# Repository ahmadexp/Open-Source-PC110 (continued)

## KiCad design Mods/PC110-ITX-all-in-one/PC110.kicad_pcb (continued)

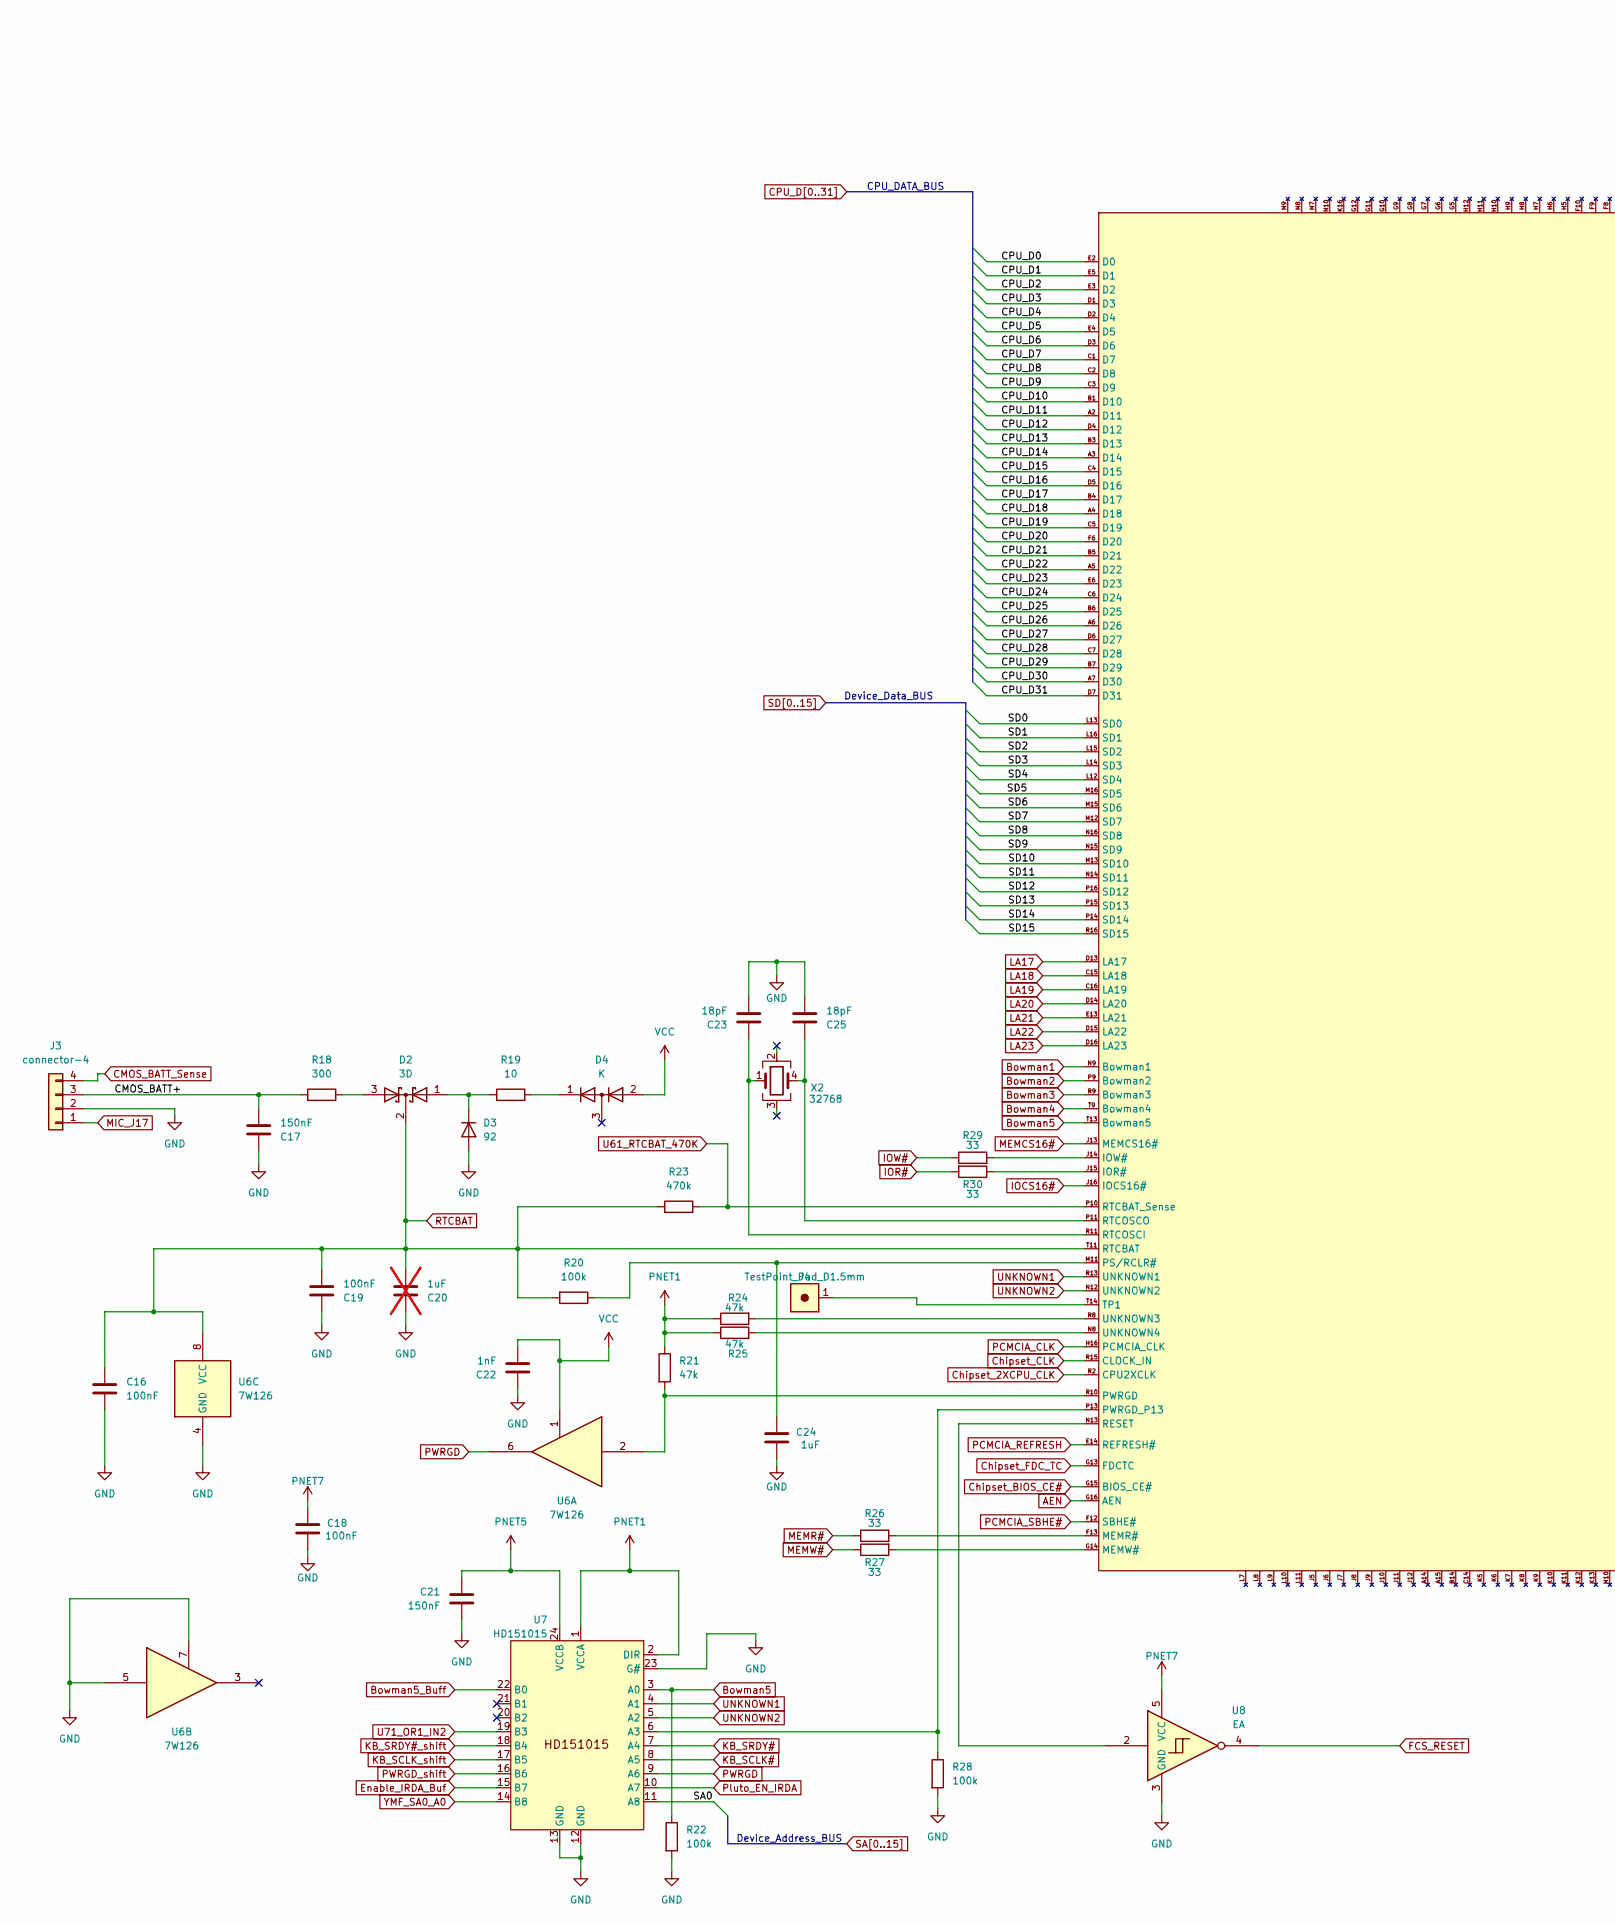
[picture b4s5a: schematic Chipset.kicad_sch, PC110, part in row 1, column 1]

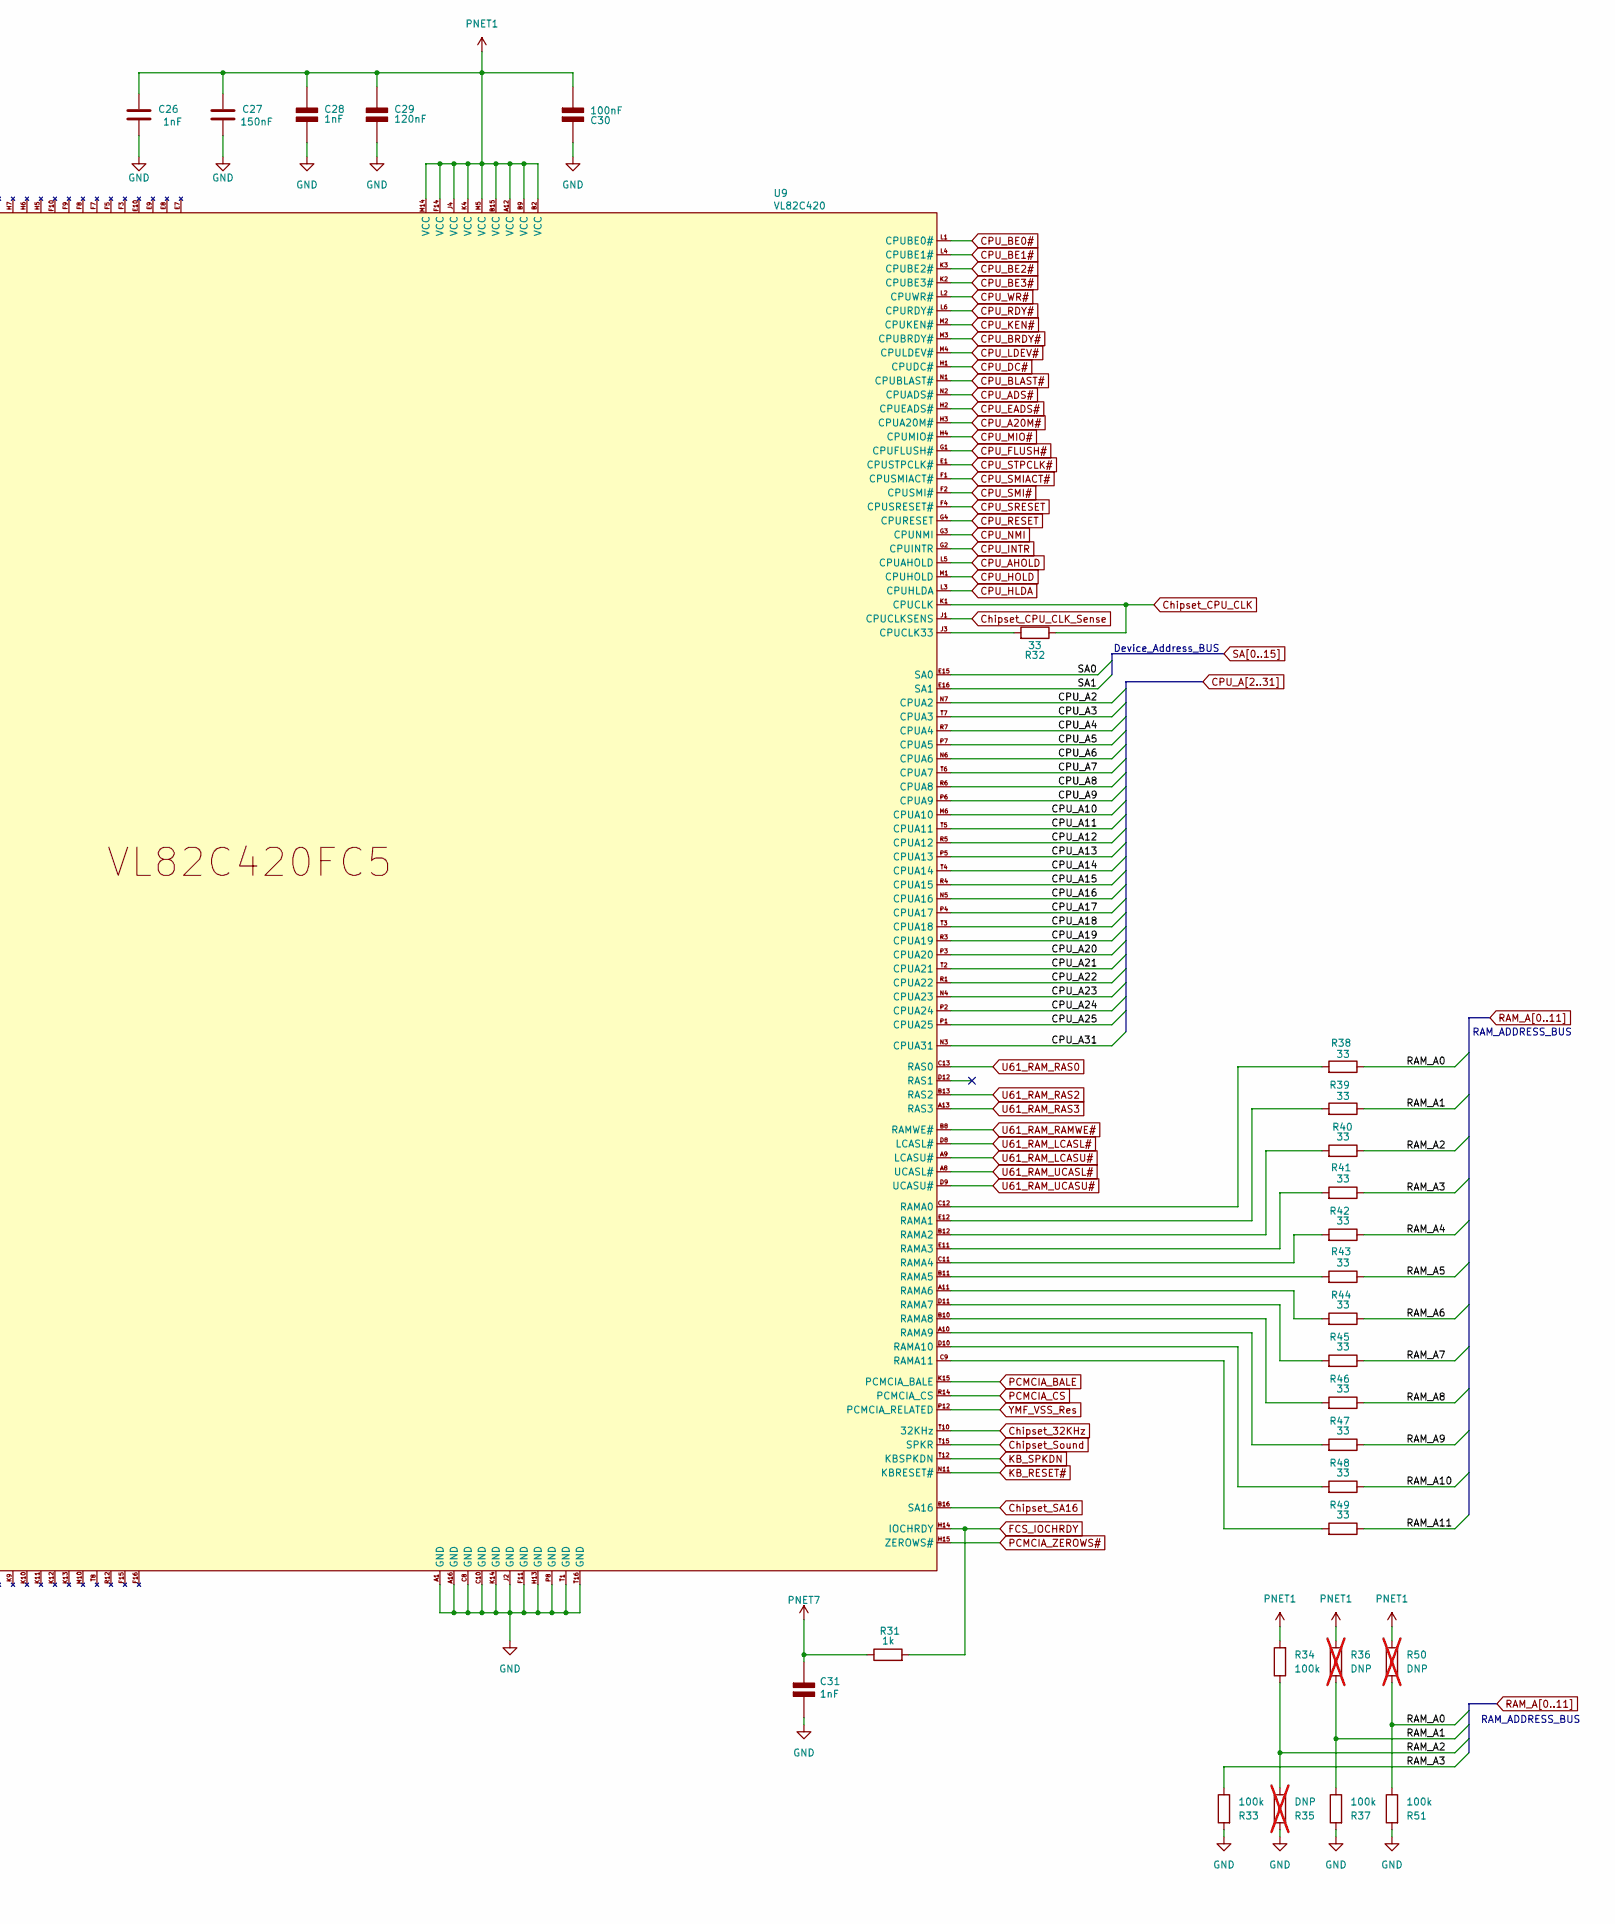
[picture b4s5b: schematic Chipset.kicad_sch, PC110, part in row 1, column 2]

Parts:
C16, C18, C19, C30: 100nF; C_0402_1005Metric
C17, C21, C27: 150nF; C_0402_1005Metric
C20: 1uF; C_0603_1608Metric; not fitted
C22, C26, C28, C31: 1nF; C_0402_1005Metric
C23, C25: 18pF; C_0402_1005Metric
C24: 1uF; C_0603_1608Metric
C29: 120nF; C_0402_1005Metric
D2: 3D
D3: 92; D_0603_1608Metric
D4: K; SOT-416L
J3: connector-4
J4: TestPoint_Pad_D1.5mm
R18: 300; R_0402_1005Metric
R19: 10; R_0402_1005Metric
R20, R22, R28, R33, R34, R37, R51: 100k; R_0402_1005Metric
R21, R24, R25: 47k; R_0402_1005Metric
R23: 470k; R_0402_1005Metric
R26, R27, R29, R30, R32, R38, R39, R40, R41, R42, R43, R44, R45, R46, R47, R48, R49: 33; R_0402_1005Metric
R31: 1k; R_0402_1005Metric
R35, R36, R50: DNP; R_0402_1005Metric; not fitted
U6: 7W126; sso-8
U7: HD151015; TSSOP-24_6.1x7.8mm_P0.65mm
U8: EA; SOT-353
U9: VL82C420; BGA-256
X2: 32768; XTAL-3

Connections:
/Chipset/CMOS_BATT+: C17.1, J3.3, R18.2
AEN: U9.G16 (AEN); also elsewhere on the board
Bowman1: U9.N9 (Bowman1); also elsewhere on the board
Bowman2: U9.P9 (Bowman2); also elsewhere on the board
Bowman3: U9.R9 (Bowman3); also elsewhere on the board
Bowman4: U9.T9 (Bowman4); also elsewhere on the board
Bowman5: R22.1, U7.3 (A0), U9.T13 (Bowman5); also elsewhere on the board
Bowman5_Buff: U7.22 (B0); also elsewhere on the board
CMOS_BATT_Sense: J3.4; also elsewhere on the board
CPU_A2: U9.N7 (CPUA2); also elsewhere on the board
CPU_A3: U9.T7 (CPUA3); also elsewhere on the board
CPU_A4: U9.R7 (CPUA4); also elsewhere on the board
CPU_A5: U9.P7 (CPUA5); also elsewhere on the board
CPU_A6: U9.N6 (CPUA6); also elsewhere on the board
CPU_A7: U9.T6 (CPUA7); also elsewhere on the board
CPU_A8: U9.R6 (CPUA8); also elsewhere on the board
CPU_A9: U9.P6 (CPUA9); also elsewhere on the board
CPU_A10: U9.M6 (CPUA10); also elsewhere on the board
CPU_A11: U9.T5 (CPUA11); also elsewhere on the board
CPU_A12: U9.R5 (CPUA12); also elsewhere on the board
CPU_A13: U9.P5 (CPUA13); also elsewhere on the board
CPU_A14: U9.T4 (CPUA14); also elsewhere on the board
CPU_A15: U9.R4 (CPUA15); also elsewhere on the board
CPU_A16: U9.N5 (CPUA16); also elsewhere on the board
CPU_A17: U9.P4 (CPUA17); also elsewhere on the board
CPU_A18: U9.T3 (CPUA18); also elsewhere on the board
CPU_A19: U9.R3 (CPUA19); also elsewhere on the board
CPU_A20: U9.P3 (CPUA20); also elsewhere on the board
CPU_A20M#: U9.H3 (CPUA20M#); also elsewhere on the board
CPU_A21: U9.T2 (CPUA21); also elsewhere on the board
CPU_A22: U9.R1 (CPUA22); also elsewhere on the board
CPU_A23: U9.N4 (CPUA23); also elsewhere on the board
CPU_A24: U9.P2 (CPUA24); also elsewhere on the board
CPU_A25: U9.P1 (CPUA25); also elsewhere on the board
CPU_A31: U9.N3 (CPUA31); also elsewhere on the board
CPU_ADS#: U9.N2 (CPUADS#); also elsewhere on the board
CPU_AHOLD: U9.L5 (CPUAHOLD); also elsewhere on the board
CPU_BE0#: U9.L1 (CPUBE0#); also elsewhere on the board
CPU_BE1#: U9.L4 (CPUBE1#); also elsewhere on the board
CPU_BE2#: U9.K3 (CPUBE2#); also elsewhere on the board
CPU_BE3#: U9.K2 (CPUBE3#); also elsewhere on the board
CPU_BLAST#: U9.N1 (CPUBLAST#); also elsewhere on the board
CPU_BRDY#: U9.M3 (CPUBRDY#); also elsewhere on the board
CPU_D0: U9.E2 (D0); also elsewhere on the board
CPU_D1: U9.E5 (D1); also elsewhere on the board
CPU_D2: U9.E3 (D2); also elsewhere on the board
CPU_D3: U9.D1 (D3); also elsewhere on the board
CPU_D4: U9.D2 (D4); also elsewhere on the board
CPU_D5: U9.E4 (D5); also elsewhere on the board
CPU_D6: U9.D3 (D6); also elsewhere on the board
CPU_D7: U9.C1 (D7); also elsewhere on the board
CPU_D8: U9.C2 (D8); also elsewhere on the board
CPU_D9: U9.C3 (D9); also elsewhere on the board
CPU_D10: U9.B1 (D10); also elsewhere on the board
CPU_D11: U9.A2 (D11); also elsewhere on the board
CPU_D12: U9.D4 (D12); also elsewhere on the board
CPU_D13: U9.B3 (D13); also elsewhere on the board
CPU_D14: U9.A3 (D14); also elsewhere on the board
CPU_D15: U9.C4 (D15); also elsewhere on the board
CPU_D16: U9.D5 (D16); also elsewhere on the board
CPU_D17: U9.B4 (D17); also elsewhere on the board
CPU_D18: U9.A4 (D18); also elsewhere on the board
CPU_D19: U9.C5 (D19); also elsewhere on the board
CPU_D20: U9.F6 (D20); also elsewhere on the board
CPU_D21: U9.B5 (D21); also elsewhere on the board
CPU_D22: U9.A5 (D22); also elsewhere on the board
CPU_D23: U9.E6 (D23); also elsewhere on the board
CPU_D24: U9.C6 (D24); also elsewhere on the board
CPU_D25: U9.B6 (D25); also elsewhere on the board
CPU_D26: U9.A6 (D26); also elsewhere on the board
CPU_D27: U9.D6 (D27); also elsewhere on the board
CPU_D28: U9.C7 (D28); also elsewhere on the board
CPU_D29: U9.B7 (D29); also elsewhere on the board
CPU_D30: U9.A7 (D30); also elsewhere on the board
CPU_D31: U9.D7 (D31); also elsewhere on the board
CPU_DC#: U9.H1 (CPUDC#); also elsewhere on the board
CPU_EADS#: U9.H2 (CPUEADS#); also elsewhere on the board
CPU_FLUSH#: U9.G1 (CPUFLUSH#); also elsewhere on the board
CPU_HLDA: U9.L3 (CPUHLDA); also elsewhere on the board
CPU_HOLD: U9.M1 (CPUHOLD); also elsewhere on the board
CPU_INTR: U9.G2 (CPUINTR); also elsewhere on the board
CPU_KEN#: U9.M2 (CPUKEN#); also elsewhere on the board
CPU_LDEV#: U9.M4 (CPULDEV#); also elsewhere on the board
CPU_MIO#: U9.H4 (CPUMIO#); also elsewhere on the board
CPU_NMI: U9.G3 (CPUNMI); also elsewhere on the board
CPU_RDY#: U9.L6 (CPURDY#); also elsewhere on the board
CPU_RESET: U9.G4 (CPURESET); also elsewhere on the board
CPU_SMI#: U9.F2 (CPUSMI#); also elsewhere on the board
CPU_SMIACT#: U9.F1 (CPUSMIACT#); also elsewhere on the board
CPU_SRESET: U9.F4 (CPUSRESET#); also elsewhere on the board
CPU_STPCLK#: U9.E1 (CPUSTPCLK#); also elsewhere on the board
CPU_WR#: U9.L2 (CPUWR#); also elsewhere on the board
Chipset_2XCPU_CLK: U9.R2 (CPU2XCLK); also elsewhere on the board
Chipset_32KHz: U9.T10 (32KHz); also elsewhere on the board
Chipset_BIOS_CE#: U9.G15 (BIOS_CE#); also elsewhere on the board
Chipset_CLK: U9.R15 (CLOCK_IN); also elsewhere on the board
Chipset_CPU_CLK: R32.1, U9.K1 (CPUCLK); also elsewhere on the board
Chipset_CPU_CLK_Sense: U9.J1 (CPUCLKSENS); also elsewhere on the board
Chipset_FDC_TC: U9.G13 (FDCTC); also elsewhere on the board
Chipset_SA16: U9.B16 (SA16); also elsewhere on the board
Chipset_Sound: U9.T15 (SPKR); also elsewhere on the board
Enable_IRDA_Buf: U7.15 (B7); also elsewhere on the board
FCS_IOCHRDY: R31.2, U9.H14 (IOCHRDY); also elsewhere on the board
FCS_RESET: U8.4; also elsewhere on the board
GND: C16.1, C17.2, C18.2, C19.2, C20.2, C21.1, C22.2, C23.1, C24.2, C25.1, C26.2, C27.2, C28.1 (+), C29.1 (+), C30.2 (-), C31.2 (-), D3.2 (A), J3.2, R22.2, R28.2, R33.2, R35.2, R37.2, R51.2, U6.4 (GND), U6.5, U6.7, U7.12 (GND), U7.13 (GND), U7.23 (G#), U8.3 (GND), U9.A1 (GND), U9.A16 (GND), U9.C8 (GND), U9.C10 (GND), U9.F11 (GND), U9.H13 (GND), U9.J2 (GND), U9.K14 (GND), U9.P8 (GND), U9.T1 (GND), U9.T16 (GND); also elsewhere on the board
IOCS16#: U9.J16 (IOCS16#); also elsewhere on the board
IOR#: R30.2; also elsewhere on the board
IOW#: R29.1; also elsewhere on the board
KB_RESET#: U9.N11 (KBRESET#); also elsewhere on the board
KB_SCLK#: U7.8 (A5); also elsewhere on the board
KB_SCLK_shift: U7.17 (B5); also elsewhere on the board
KB_SPKDN: U9.T12 (KBSPKDN); also elsewhere on the board
KB_SRDY#: U7.7 (A4); also elsewhere on the board
KB_SRDY#_shift: U7.18 (B4); also elsewhere on the board
LA17: U9.D13 (LA17); also elsewhere on the board
LA18: U9.C15 (LA18); also elsewhere on the board
LA19: U9.C16 (LA19); also elsewhere on the board
LA20: U9.D14 (LA20); also elsewhere on the board
LA21: U9.E13 (LA21); also elsewhere on the board
LA22: U9.D15 (LA22); also elsewhere on the board
LA23: U9.D16 (LA23); also elsewhere on the board
MEMCS16#: U9.J13 (MEMCS16#); also elsewhere on the board
MEMR#: R26.1; also elsewhere on the board
MEMW#: R27.1; also elsewhere on the board
MIC_J17: J3.1; also elsewhere on the board
unnamed: D2.3 (A), R18.1
unnamed: D2.1 (A), D3.1 (K), R19.1
unnamed: D4.1 (K), R19.2
unnamed: R28.1, U7.6 (A3), U9.P13 (PWRGD_P13)
unnamed: R32.2, U9.J3 (CPUCLK33)
unnamed: R30.1, U9.J15 (IOR#)
unnamed: R29.2, U9.J14 (IOW#)
unnamed: R26.2, U9.F13 (MEMR#)
unnamed: R27.2, U9.G14 (MEMW#)
unnamed: C24.1, R20.1, U9.M11 (PS/RCLR#)
unnamed: R21.2, U6.2, U9.R10 (PWRGD)
unnamed: R38.2, U9.C12 (RAMA0)
unnamed: R39.2, U9.E12 (RAMA1)
unnamed: R40.2, U9.B12 (RAMA2)
unnamed: R41.2, U9.E11 (RAMA3)
unnamed: R42.2, U9.C11 (RAMA4)
unnamed: R43.2, U9.B11 (RAMA5)
unnamed: R44.2, U9.A11 (RAMA6)
unnamed: R45.2, U9.D11 (RAMA7)
unnamed: R46.2, U9.B10 (RAMA8)
unnamed: R47.2, U9.A10 (RAMA9)
unnamed: R48.2, U9.D10 (RAMA10)
unnamed: R49.2, U9.C9 (RAMA11)
unnamed: U8.2, U9.N13 (RESET)
unnamed: C23.2, U9.R11 (RTCOSCI), X2.1
unnamed: C25.2, U9.P11 (RTCOSCO), X2.4
unnamed: J4.1, U9.T14 (TP1)
unnamed: R24.2, U9.R8 (UNKNOWN3)
unnamed: R25.2, U9.N8 (UNKNOWN4)
PCMCIA_BALE: U9.K15 (PCMCIA_BALE); also elsewhere on the board
PCMCIA_CLK: U9.H16 (PCMCIA_CLK); also elsewhere on the board
PCMCIA_CS: U9.R14 (PCMCIA_CS); also elsewhere on the board
PCMCIA_REFRESH: U9.E14 (REFRESH#); also elsewhere on the board
PCMCIA_SBHE#: U9.F12 (SBHE#); also elsewhere on the board
PCMCIA_ZEROWS#: U9.H15 (ZEROWS#); also elsewhere on the board
PNET1: C26.1, C27.1, C28.2 (-), C29.2 (-), C30.1 (+), R21.1, R24.1, R25.1, R34.2, R36.2, R50.2, U7.1 (VCCA), U7.2 (DIR), U9.A12 (VCC), U9.B2 (VCC), U9.B9 (VCC), U9.B15 (VCC), U9.F14 (VCC), U9.J4 (VCC), U9.K4 (VCC), U9.M5 (VCC), U9.M14 (VCC); also elsewhere on the board
PNET5: C21.2, U7.24 (VCCB); also elsewhere on the board
PNET7: C18.1, C31.1 (+), R31.1, U8.5 (VCC); also elsewhere on the board
PWRGD: U6.6, U7.9 (A6); also elsewhere on the board
PWRGD_shift: U7.16 (B6); also elsewhere on the board
Pluto_EN_IRDA: U7.10 (A7); also elsewhere on the board
RAM_A0: R38.1, R50.1, R51.1; also elsewhere on the board
RAM_A1: R36.1, R37.1, R39.1; also elsewhere on the board
RAM_A2: R34.1, R35.1, R40.1; also elsewhere on the board
RAM_A3: R33.1, R41.1; also elsewhere on the board
RAM_A4: R42.1; also elsewhere on the board
RAM_A5: R43.1; also elsewhere on the board
RAM_A6: R44.1; also elsewhere on the board
RAM_A7: R45.1; also elsewhere on the board
RAM_A8: R46.1; also elsewhere on the board
RAM_A9: R47.1; also elsewhere on the board
RAM_A10: R48.1; also elsewhere on the board
RAM_A11: R49.1; also elsewhere on the board
RTCBAT: C16.2, C19.1, C20.1, D2.2 (K), R20.2, R23.2, U6.8 (VCC), U9.T11 (RTCBAT); also elsewhere on the board
SA0: U7.11 (A8), U9.E15 (SA0); also elsewhere on the board
SA1: U9.E16 (SA1); also elsewhere on the board
SD0: U9.L13 (SD0); also elsewhere on the board
SD1: U9.L16 (SD1); also elsewhere on the board
SD2: U9.L15 (SD2); also elsewhere on the board
SD3: U9.L14 (SD3); also elsewhere on the board
SD4: U9.L12 (SD4); also elsewhere on the board
SD5: U9.M16 (SD5); also elsewhere on the board
SD6: U9.M15 (SD6); also elsewhere on the board
SD7: U9.M12 (SD7); also elsewhere on the board
SD8: U9.N16 (SD8); also elsewhere on the board
SD9: U9.N15 (SD9); also elsewhere on the board
SD10: U9.M13 (SD10); also elsewhere on the board
SD11: U9.N14 (SD11); also elsewhere on the board
SD12: U9.P16 (SD12); also elsewhere on the board
SD13: U9.P15 (SD13); also elsewhere on the board
SD14: U9.P14 (SD14); also elsewhere on the board
SD15: U9.R16 (SD15); also elsewhere on the board
U61_RAM_LCASL#: U9.D8 (LCASL#); also elsewhere on the board
U61_RAM_LCASU#: U9.A9 (LCASU#); also elsewhere on the board
U61_RAM_RAMWE#: U9.B8 (RAMWE#); also elsewhere on the board
U61_RAM_RAS0: U9.C13 (RAS0); also elsewhere on the board
U61_RAM_RAS2: U9.B13 (RAS2); also elsewhere on the board
U61_RAM_RAS3: U9.A13 (RAS3); also elsewhere on the board
U61_RAM_UCASL#: U9.A8 (UCASL#); also elsewhere on the board
U61_RAM_UCASU#: U9.D9 (UCASU#); also elsewhere on the board
U61_RTCBAT_470K: R23.1, U9.P10 (RTCBAT_Sense); also elsewhere on the board
U71_OR1_IN2: U7.19 (B3); also elsewhere on the board
UNKNOWN1: U7.4 (A1), U9.R13 (UNKNOWN1)
UNKNOWN2: U7.5 (A2), U9.N12 (UNKNOWN2)
VCC: C22.1, D4.2 (A), U6.1; also elsewhere on the board
YMF_SA0_A0: U7.14 (B8); also elsewhere on the board
YMF_VSS_Res: U9.P12 (PCMCIA_RELATED); also elsewhere on the board

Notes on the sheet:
CPU_DATA_BUS
Device_Data_BUS
Device_Address_BUS
RAM_ADDRESS_BUS
